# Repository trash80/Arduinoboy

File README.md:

# Arduinoboy
Official ArduinoBoy Repository for serial MIDI communication to the Nintendo Gameboy.

## About 
Arduinoboy is software for the [Arduino hardware platform](http://arduino.cc) that allows serial communication (MIDI) to the Nintendo Gameboy for music applications such as [LittleSoundDJ](http://littlesounddj.com), [Nanoloop.](http://www.nanoloop.com/), and [mGB](https://github.com/trash80/mGB)

## Current Features
* Affordable and easily accessible parts for assembly.
* Accurate MIDI Sync, Start and Stop commands.
* Push Button selector sets the sync/state modes [(7 modes available)](#modes-details)
* [mGB](https://github.com/trash80/mGB)
 Mode: Full MIDI in support across all Gameboy Channels, including a unique "poly" mode allows you to play your Game Boy like a synthesizer. 
* Midi Out Doubles as a Midi Thru
* "Filtering" data for only sync messages, no dedicated MIDI line required.
* Can be powered by the Game Boy's gamelink port.
* USB upgradeable via Arduino.
* Midi settings configurable using a Mac/PC editor built in Max.
* Tested and works with DMG (Original), Gameboy Color, and Advance/SP.

## Modes Details
#### Mode 1 - LSDJ as MIDI Slave Sync
Slave your Game Boy running [LittleSoundDJ](http://littlesounddj.com) to your midi sequencer or Digital audio workstation.  

You can send the arduinoboy midi notes to change sync resolution and start/stop the LSDJ sequencer.  

_LSDJ Slave Mode Midi Note Effects:_

* 48 - `C-2` Sends a Sequencer Start Command
* 49 - `C#2` Sends a Sequencer Stop Command
* 50 - `D-2` Toggles Normal Tempo 
* 51 - `D#2` Toggles 1/2 Tempo
* 52 - `E-2` Toggles 1/4 Tempo
* 53 - `F-2` Toggles 1/8 Tempo

Higher note values than these map LSDJ song position row offset on a Song Start.

In LSDJ the `sync` mode should be set to `Slave`
 
#### Mode 2 LSDJ as MIDI Master Sync. 

Send Midi sync with LSDJ as a midi clock master, LSDJ also sends a Midi Note on message that corresponds to the song row number on play.

In LSDJ the `sync` mode should be set to `Master`

#### Mode 3 LSDJ PC Keyboard mode.
This mode emulates the [PC Keyboard Mode](http://littlesounddj.wikia.com/wiki/PC_Keyboard_Interface) built into LSDJ, allowing you to control the following aspects of LSDJ: 

Features:

* The first octave controls M-U-T-E, 
* Cursor control (LSDJ Live mode only), 
* Table selection
* Table cue.

_PC Keyboard mode midi note map_

* 36 - `C-1` Mute Pu1 Off/On
* 37 - `C#1` Mute Pu2 Off/On
* 38 - `D-1` Mute Wav Off/On
* 39 - `D#1` Mute Noi Off/On
* 40 - `E-1` Livemode Cue Sequence
* 41 - `F-1` Livemode Cursor Up
* 42 - `F#1` Livemode Cursor Down
* 43 - `G-1` Livemode Cursor Left
* 44 - `G#1` Live mode Cursor Right
* 45 - `A-1` Table Up
* 46 - `A#1` Table Down
* 47 - `B-1` Cue Table
* 48+ - Notes from this note up will accept midi in from an external keyboard or sequencer and allow you to play the notes`C-2 to C-8`.  
* Midi Program Change messages will select from instrument table
* Default Midi channel is 16. You can set this in the top of the main source file in the archive, or via the [Max Pat editor](#max).

In LSDJ the `sync` mode should be set to `Keyboard`

#### Mode 4 MIDI to Nanoloop sync
Sync [Nanoloop.](http://www.nanoloop.com/) to external midi clock signals sent to the midi in.

In Nanoloop, the sync mode should be set to `slave`.

#### Mode 5 Full MIDI with mGB
[mGB](https://github.com/trash80/mGB) is a Gameboy cartridge program (You need a Flash Cart and Transfer hardware) That enables the Gameboy to act as a MIDI supported sound module that allows full control of the Game Boy sound hardware. 

It works with the old DMG Gameboy as well as GBC/GBA.

#### Mode 6 LSDJ MIDIMAP 
Lsdj will sync to incoming MIDI sync, and incoming MIDI notes are mapped to LSDJ's song row #. The currently selected row's MIDI note is displayed on the top right of the LSDJ screen, and incoming MIDI notes will also display the relative song row number in the same location.

In LSDJ the `sync` mode should be set to `MI.MAP`. 

*This requires a special version of LSDJ, which can be found in your account on the [LSDJ website](http://littlesounddj.com/lsd/latest/full_version/).*

#### Mode 7 LSDJ MIDIOUT
Each of the 4 gameboy channels send MIDI data on 4 midi channels by the use of effects commands:

* `Nxx` - Sends a MIDI Note - Absolute to the value placed in the effect. N00 sends note off, `N01`-`N6F` send midi notes 1 to 112.
* `Qxx` - Sends a [MIDI Note](http://www.electronics.dit.ie/staff/tscarff/Music_technology/midi/midi_note_numbers_for_octaves.htm) relative to the current channel's pitch. The effect value is a offset. so `Q0C` in `PU1` would send a note 1 octave higher than what `PU1` is currently playing. This is useful as a table command to track midi notes as normal notes in the sequencer.
* `Xxx` - Sends a MIDI CC - By default in Arduinoboy the high nibble selects a CC#, and the low nibble sends a value `0-F` to `0-127`. This can be changed to allow just 1 midi CC with a range of `00`-`6F`, or 7 CCs with scaled or unscaled values.
* `Yxx` - Sends a program/patch/preset change.

By default each channel of LSDJ is mapped to midi channels 1-4. For example note commands from PU1 will be sent to midi channel 1. 

In LSDJ the `sync` mode should be set to `Midiout`. 

*This requires a special version of LSDJ, which can be found in your account on the [LSDJ website](http://littlesounddj.com/lsd/latest/full_version/).*

## Max Editor

[The Arduinoboy Editor for Max](https://github.com/trash80/Arduinoboy/tree/master/Editor) for PC/OSX machines is a gui editor that allows you to edit the various global midi settings of your arduinoboy without editing or flashing code, over midi. It used to required the now deprecated Max Runtime, but you can also run it using a demo of [Cycling '74's Max application](https://cycling74.com/downloads/)

### Maxpat Settings
* `Midi In/Out`
Connect your arduinoboy to these ports on your system. Once it has connected, all the lights on your arduinoboy should flash in order, and the editor will show a green `Connected`.
* `Mode` 
Setting this will tell your arduinoboy what mode to boot into automatically. This is handy if you built your own arduinoboy and decided you wanted to skimp out on LEDs and a button.
* `LSDJ Slave Mode settings` - The midi channel LSDJ slave mode will receive its commands on.
* `LSDJ Master Mode settings` - The midi channel LSDJ Master mode will send its midi notes mapped to row number on.
* `Keyboard Mode settings` - What channel LSDJ will look for its keyboard mode midi commands. No idea what compatibility mode does.
* `mGB midi settings` - Map each incoming midi channel to a specific Gameboy channel in mGB.
* `LSDJ Livesync/Livemap settings` - The midi channel Livesync/Livemap will listen to incoming midi commands from.
* `LSDJ Midiout settings` - Here you can set the following:
	* `Note midi channel` -  The channel each LSDJ channel will send it's midi note commands on.
	* `CC midi channel` -  The channel each LSDJ channel will send it's Continuous Controller commands on.
	* `CC 0` - The initial CC each channel will send. The type of data it will send is based on the next setting.
	* `CC Mode` - Game Boys have limitations! You can either have arduinoboy send one CC with many values, or 7 with limited 8bit values. By default in Arduinoboy the high nibble selects a CC#, and the low nibble sends a value [0-F] to [0-127]. This can be changed to allow just 1 midi CC with a range of 00-6F, or 7 CCs with scaled or unscaled values.
	* `CC Scaling ` - Set wether the 7 CCs are scaled or unscaled.

## Future Features & wishlist
  * Build instructions, and a Arduino Shield

## How To build an Arduinoboy

* [Build Photos](http://flickr.com/photos/trash80/2316803175/in/set-72157604068871573/)
* [Old version (Pre 1.1.0)](http://trash80.net/junkfood/arduinoboy/arduinoboy-schem-v.0.9.8-r1.png)

### Video Demos

  * [Keyboard Mode Test](http://youtube.com/watch?v=TnLUuvc78XY)
  * [Sync Demos](http://youtube.com/watch?v=iVmhy-Lo7BI)
  * [Arduino inside of Gameboy DMG](http://youtube.com/watch?v=VwrMuOA0VnY)
  * [mGB Example & Arduinoboy build into a DMG](http://vimeo.com/1853931)
  * [PDF explores mGB with a MIDI guitar](http://www.youtube.com/watch?v=HAU9MzZ2qeE)

## Thanks To
  * [Arduino](http://arduino.cc)
  * [Nitro2k01](http://blog.gg8.se/wordpress/) for ASM help with mGB 
  * [GWEM](http://www.preromanbritain.com/gwem/lsdj_midi/g33k.html) g33k page
  * [Midines](http://wayfar.net) Thanks for the help x|k!
  * [firestARTer](http://www.firestarter-music.de) help with keyboard & Midi handling information. 
  * [Gijs Gieskes](http://gieskes.nl) Found source code that gave insight into Nanoloop sync
  * [Little Sound DJ](http://littlesounddj.com)
  * [http://devrs.com/gb](http://devrs.com/gb) Madcatz PC link port for gb serial specs
  * [http://chipmusic.org](http://chipmusic.org) For all things Chipmusic.

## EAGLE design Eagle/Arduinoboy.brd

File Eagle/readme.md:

# Change log

### 1.1.3
 - Changed status mode names

### 1.1.2
 - Fixed PS/2 connection

### 1.1.1
 - Fixed MIDI jack spacing

### 1.1.0
 - Added PS/2 jack for LSDJ keyboard input
 - Removed screw terminals (nobody used them)
 - Replaced MIDI jacks with Jazzmarazz's move versatile footprint
 - Move button and status LED to make room for PS/2 jack

### 1.0.1
 - Fixed GB link port SIN/SOUT pins
 - Fixed routing error causing a bridge between LEDs

### 1.0.0
 - Initial version
 - Added GBC link port for easier use
 - Added screw terminals by request
 - Replaced most components from familiar's design

### 0.0.1
 - Beta/test release
 - Used familiar's design

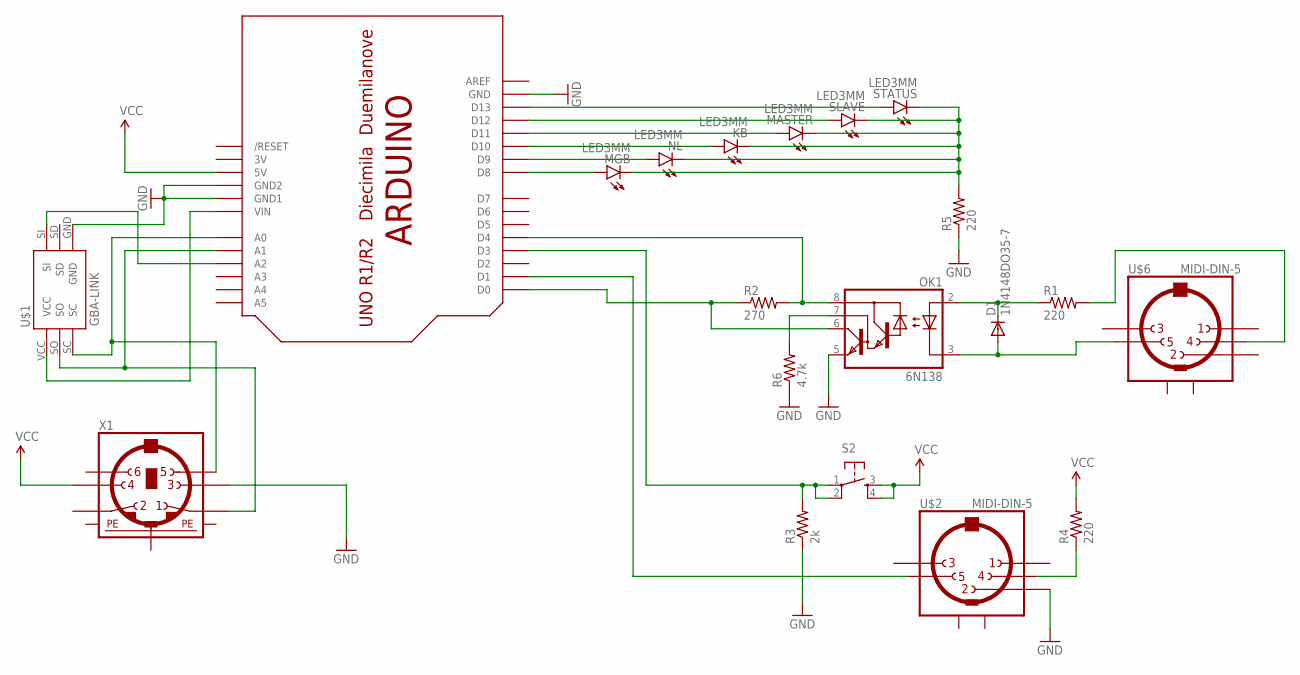
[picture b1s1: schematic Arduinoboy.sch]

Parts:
D1: 1N4148DO35-7; DO35-7
KB: LED3MM
MASTER: LED3MM
MGB: LED3MM
NL: LED3MM
OK1: 6N138; DIL08
R1, R4, R5: 220; AXIAL-0.3
R2: 270; AXIAL-0.3
R3: 2k; AXIAL-0.3
R6: 4.7k; AXIAL-0.3
S2: TAC_SWITCHPTH; TACTILE-PTH
SLAVE: LED3MM
STATUS: LED3MM
U$1: GBA-LINK
U$2, U$6: MIDI-DIN-5
U$3: ARDUINOUNO; ARDUINO
X1: MINI_DIN_6; M_DIN6

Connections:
3V: U$3.3V
GND: OK1.5 (GND), R3.P$1 (1), R5.P$1 (1), R6.P$1 (1), U$1.GND, U$2.2, U$3.GND, U$3.GND1, U$3.GND2, X1.3
unnamed: D1.C, OK1.2 (A), R1.P$1 (1)
unnamed: D1.A, OK1.3 (C), U$6.5
unnamed: R3.P$2 (2), S2.1, S2.2, U$3.D3
unnamed: R4.P$1 (1), U$2.4
unnamed: MGB.A, U$3.D8
unnamed: U$2.5, U$3.D1
unnamed: NL.A, U$3.D9
unnamed: OK1.8 (VCC), R2.P$2 (2), U$3.D4
unnamed: OK1.6 (VO), R2.P$1 (1), U$3.D0
unnamed: KB.A, U$3.D10
unnamed: MASTER.A, U$3.D11
unnamed: SLAVE.A, U$3.D12
unnamed: STATUS.A, U$3.D13
unnamed: KB.K (C), MASTER.K (C), MGB.K (C), NL.K (C), R5.P$2 (2), SLAVE.K (C), STATUS.K (C)
unnamed: OK1.7 (VB), R6.P$2 (2)
unnamed: U$1.SC, U$3.A0, X1.5
unnamed: U$1.VCC, U$3.VIN
unnamed: R1.P$2 (2), U$6.4
unnamed: U$1.SO, U$3.A1, X1.1
unnamed: U$1.SI, U$3.A2
PE1: X1.SH1 (PE1)
PE2: X1.SH2 (PE2)
PE3: X1.SH3 (PE3)
VCC: R4.P$2 (2), S2.3, S2.4, U$3.5V, X1.4

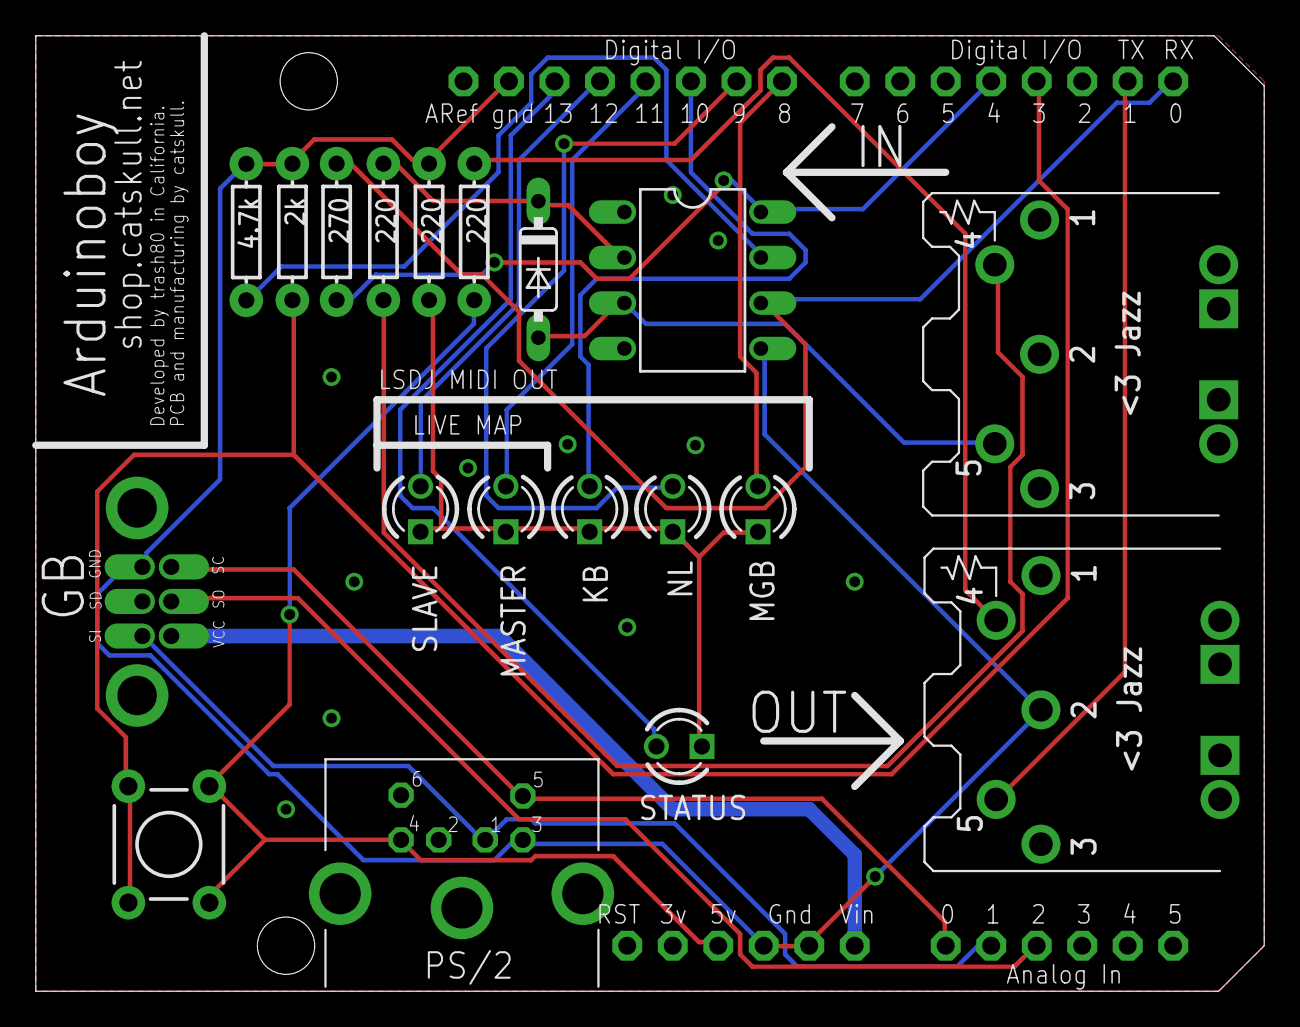
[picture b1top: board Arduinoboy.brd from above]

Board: 2 copper layers, 68.6 x 53.3 mm, 20 parts (0 on the bottom side), 22 nets.

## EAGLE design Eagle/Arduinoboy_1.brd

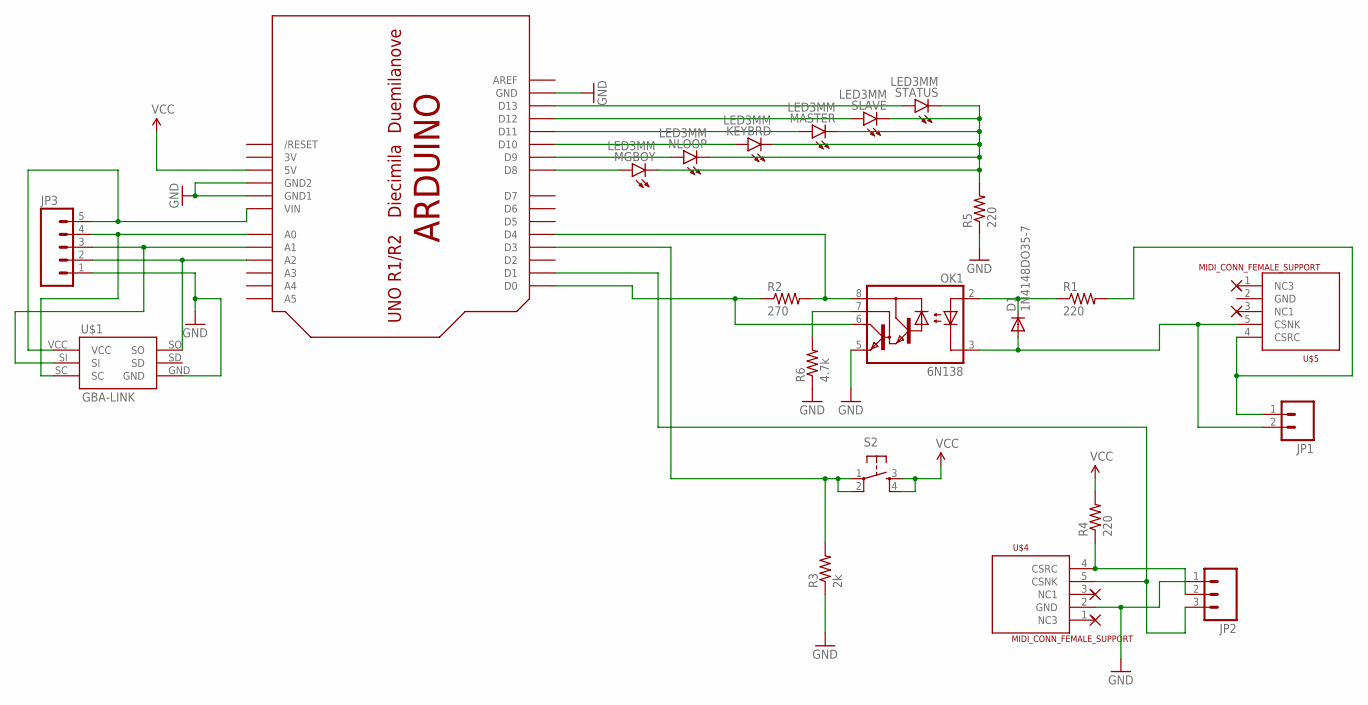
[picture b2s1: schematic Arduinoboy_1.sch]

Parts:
D1: 1N4148DO35-7; DO35-7
JP1: M025MM; SCREWTERMINAL-5MM-2
JP2: M03-SCREW-5MM; SCREWTERMINAL-5MM-3
JP3: M05SCREW; SCREWTERMINAL-3.5MM-5
KEYBRD: LED3MM
MASTER: LED3MM
MGBOY: LED3MM
NLOOP: LED3MM
OK1: 6N138; DIL08
R1, R4, R5: 220; AXIAL-0.3
R2: 270; AXIAL-0.3
R3: 2k; AXIAL-0.3
R6: 4.7k; AXIAL-0.3
S2: TAC_SWITCHPTH; TACTILE-PTH
SLAVE: LED3MM
STATUS: LED3MM
U$1: GBA-LINK
U$3: ARDUINOUNO; ARDUINO
U$4, U$5: MIDI_CONN_FEMALE_SUPPORT; DIN_5_FEMALE_SUPPORT

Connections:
3V: U$3.3V
GND: JP2.1, JP3.1, OK1.5 (GND), R3.P$1 (1), R5.P$1 (1), R6.P$1 (1), U$1.GND, U$3.GND, U$3.GND1, U$3.GND2, U$4.2 (GND)
unnamed: D1.C, OK1.2 (A), R1.P$1 (1)
unnamed: D1.A, JP1.2, OK1.3 (C), U$5.5 (CSNK)
unnamed: R3.P$2 (2), S2.1, S2.2, U$3.D3
unnamed: JP2.2, R4.P$1 (1), U$4.4 (CSRC)
unnamed: MGBOY.A, U$3.D8
unnamed: JP2.3, U$3.D1, U$4.5 (CSNK)
unnamed: NLOOP.A, U$3.D9
unnamed: OK1.8 (VCC), R2.P$2 (2), U$3.D4
unnamed: OK1.6 (VO), R2.P$1 (1), U$3.D0
unnamed: KEYBRD.A, U$3.D10
unnamed: MASTER.A, U$3.D11
unnamed: SLAVE.A, U$3.D12
unnamed: STATUS.A, U$3.D13
unnamed: KEYBRD.K (C), MASTER.K (C), MGBOY.K (C), NLOOP.K (C), R5.P$2 (2), SLAVE.K (C), STATUS.K (C)
unnamed: OK1.7 (VB), R6.P$2 (2)
unnamed: JP3.4, U$1.SC, U$3.A0
unnamed: JP1.1, R1.P$2 (2), U$5.4 (CSRC)
unnamed: JP3.3, U$1.SI, U$3.A1
unnamed: JP3.2, U$1.SO, U$3.A2
unnamed: JP3.5, U$1.VCC, U$3.VIN
VCC: R4.P$2 (2), S2.3, S2.4, U$3.5V

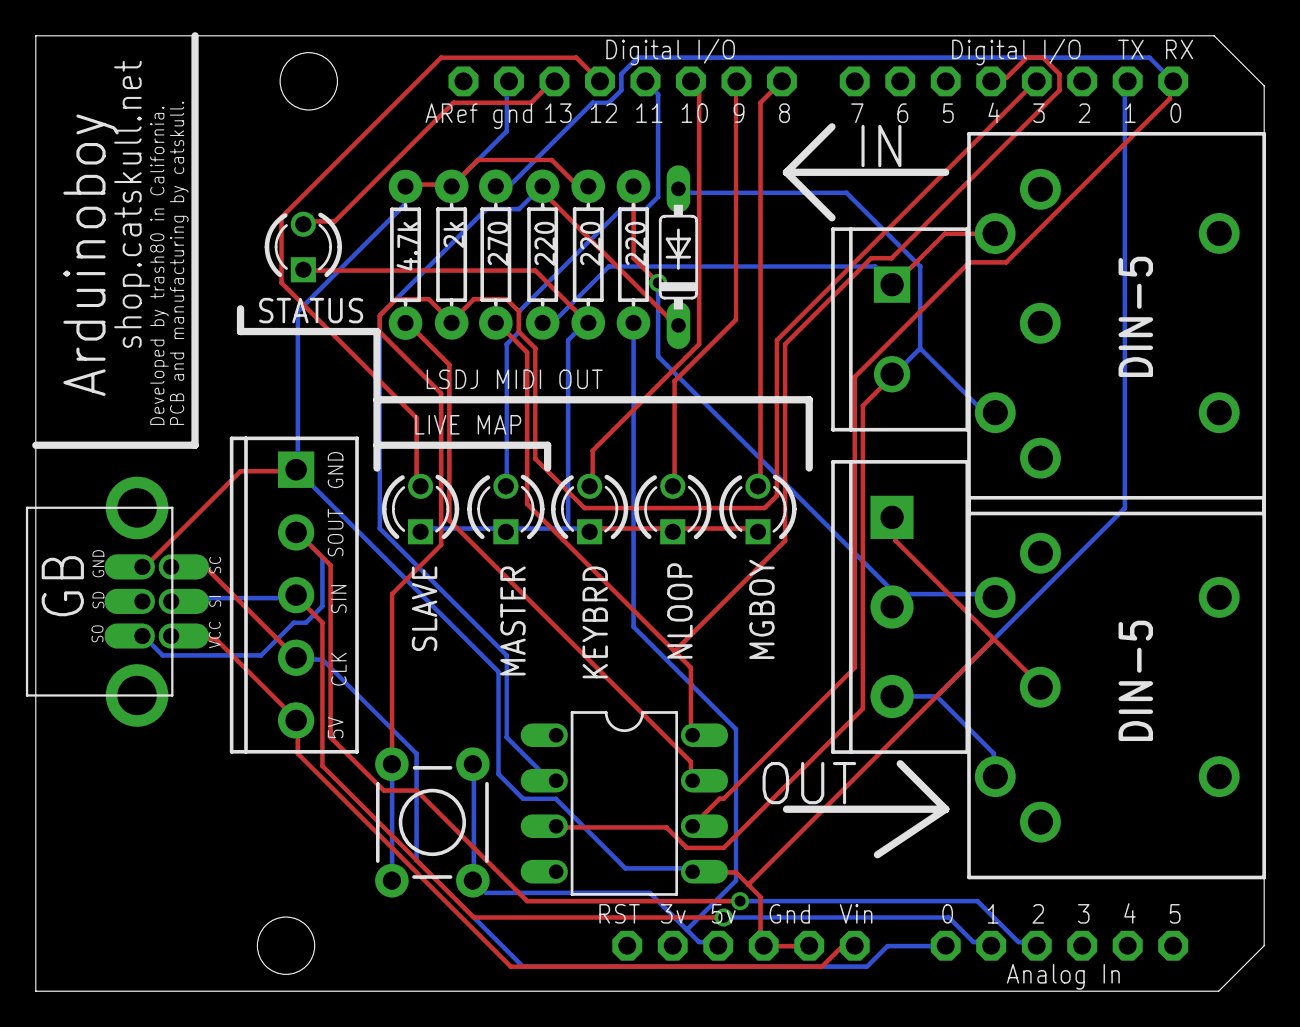
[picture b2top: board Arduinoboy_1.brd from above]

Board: 2 copper layers, 68.6 x 53.3 mm, 22 parts (0 on the bottom side), 22 nets.

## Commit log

2015-07-26 Commit 0.0.1 Alpha from Google Code.
2015-07-26 Release 0.2.1 from Google Code.
2015-07-26 Release 0.3.1 from Google Code.
2015-07-26 Release 0.3.2 from Google Code.
2015-07-26 Release 0.8.5 from Google Code.
2015-07-26 Release 0.8.6 From Google Code.
2015-07-26 Release 0.8.7 from Google Code.
2015-07-26 Release 0.9.1 from Google Code.
2015-07-26 Release 0.9.8 from Google Code.
2015-07-26 Release 0.9.9 from Google Code.
2015-07-26 Release 1.1.0 from Google Code.
2015-07-26 Release 1.0.2 from Google Code.
2015-07-26 Release 1.0.3 from Google Code.
2015-07-26 Release 1.0.4 from Google Code.
2015-07-26 Release 1.0.5 from Google Code.
2015-07-26 Release 1.1.0a from Google Code.
2015-07-26 Release 1.2.0 from Google Code.
2015-07-26 Release 1.2.1 from Google Code.
2015-07-26 Release 1.2.2 from Google Code.
2015-07-26 Release 1.2.3 from Google Code.
2015-10-23 Move news section from readme to changelog
2015-10-23 Remove news from readme
2015-10-23 Remove image of arduinoboy
2015-10-23 Add better schematic
2015-10-24 Add eagle files
2015-10-24 Add pro mini schematic
2015-10-24 Use relative links for schematic images
2015-10-25 Update eagle designs
2015-12-19 Fix PCB bugs
2015-12-19 Add WIP midi clock mode
2015-12-19 Add library part for GBC link cable port
2016-01-30 Comment out midi clock
2016-01-30 Add eagle files for v1.1.0
2016-01-30 Add eagle read
2016-03-02 Revert "Merge remote-tracking branch 'origin/master'"
    This reverts commit f80d08e31e016278268a65021739ee5e778163b8, reversing
    changes made to f40ec3e5aa5b3fbf1e4945aa6cedb9ac409a7af3.
2016-04-20 MIDIout channel switch on the fly
2016-05-14 Revert "MIDIout channel switch on the fly"
    This reverts commit fa3229989069f63edc213bdc0f0ca55e2da381b8.
2016-06-22 First attempt at using a PS/2 keyboard at the same time as midi
2016-06-22 Fix include keyboard lib
2016-06-22 Check if the incoming keyboard byte is valid
2016-07-03 Update eagle files
2016-07-10 New version of LSDJ Midi Map. Added Teensy 3.x & LC support. Added USB MIDI mode for Teensy.
2016-07-10 Uncomment of main map function.
2016-07-10 Issues with status LED.
2016-07-11 LSDJ Map mode clean up.
2016-07-11 Fixed LSDJ Map mode for note offs on LSDJ row 0.
2016-07-11 LSDJ Map mode in USB note receive logic issue.
2016-07-12 Added a resetQueue to USB sequencer start command. (clear pending sync messages)
2016-07-12 Use pin 6 for mode button
2016-07-12 Mode button pin is INPUT_PULLUP
2016-07-12 Use pin 3 for PS2 irq pin
2016-07-12 Read keyboard scan codes and send it to gameboy
2016-07-15 Changing sync map delay on USB MIDI.
2016-07-21 First!
2016-07-21 Added in new LSDJSlave class
2016-07-21 Updated editor for version 1.3
2016-07-22 Added LSDJ Master mode class.
2016-07-22 Master Sync issue.
2016-07-23 New gameboy sendBit method.
2016-07-23 Nanoloop sync added.
2016-07-23 Remove ps2 keyboard code
2016-07-23 Re add ps2 stuff
2016-07-23 Added LSDJMidiout mode.
2016-07-24 Added LSDJKeyboard Mode
2016-07-24 Added mGB mode.
2016-07-25 Change pin button
2016-07-25 Fixing LSDJ Keyboard delays.
2016-07-25 Added all notes off to LSDJ Midiout mode.
2016-07-25 no message
2016-07-30 Mode button is INPUT_PULLUP
2016-08-28 Fixing Map mode for second bank note offs.
2016-08-28 Added license.
2016-08-28 reorganization
2016-08-28 Adding synth module.
2016-08-29 Refactoring classes.
2016-08-29 removing classes.
2016-08-29 Midiout was not sending command message with channel.
2016-08-29 Fixing program change events.
2016-10-16 Fixing Teensy LC GPIOB compile issue.
2016-11-01 Add note about dependency
2016-11-14 Update Arduinoboy.ino
    Fixed comment about Teensy LED pins.
2017-03-19 Added new common setOptions method for mode classes.
2017-03-20 Updated sysex to work with Teensy 3.2 for editor.
2017-03-20 Update to editor version number.
2017-03-20 Adding send routes
2017-03-31 Update Mode_MidiGb.ino
    Fixed a bug in mGB mode preventing receiving notes via Teensy USB MIDI
2017-03-31 Update Mode_MidiGb.ino
    Fixing LED blink lights on Teensy USB MIDI.
2017-04-20 Markdown fix
    Some of the bullets for Midi out modes got futzed, so I changed them back for readability
2017-04-28 docs refactor v1
2017-04-28 First draft of a doc refactor
2017-04-28 Typo
2017-04-28 Refactoring of the docs. Feedback wanted!
2017-04-28 Maxpat screenshot
2017-04-28 fixed
2017-06-11 Fixed typo in comment for Teensy 3.2 pinouts.
2020-05-05 Corrected MIDIMAP docs
2020-05-18 Updated changelog and version number
2020-05-18 Added support for Arduino Leonardo and Due
2020-05-18 Added support for modified mGB versions with extended MIDI channels
2020-05-19 Added support for Arduino Mega 2560 and Arduino UNO Wifi
2020-05-23 Deleted PS2 port code
2020-08-09 Removing comments to fix correct values in midi CC
2020-11-16 Added Teensy 4.1 support & USB Midi Host Mode
2020-11-16 modifying so diff is legible on pull request

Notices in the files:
parts and their libraries:
SparkFun-Resistors: Licensing: Creative Commons ShareAlike 4.0 International - https://creativecommons.org/licenses/by-sa/4.0
